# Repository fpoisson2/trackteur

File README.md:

# Trackteur

Système de traceur GPS DIY pour le suivi de véhicules et équipements agricoles. Ce projet documente la création et le déploiement d'un système de suivi GPS complet, depuis le matériel jusqu'à l'infrastructure serveur.

## Vue d'ensemble de l'infrastructure

L'architecture est conçue pour être résiliente et évolutive, en s'appuyant sur des services cloud modernes pour le routage et l'hébergement.

```mermaid
flowchart TB
    subgraph tracker["Traceur GPS DIY"]
        ESP[ESP32 + GPS + 4G LTE]
    end

    subgraph cloudflare["Cloudflare"]
        WORKER[Cloudflare Worker<br/>endpoint.trackteur.cc]
    end

    subgraph servers["Serveurs Traccar (Réplication)"]
        SRV1[Serveur 1<br/>serveur1e.trackteur.cc]
        SRV2[Serveur 2<br/>serveur2.trackteur.cc]
        SRV3[Serveur 3<br/>serveur3.trackteur.cc]
    end

    tracker -->|envoie les données| cloudflare
    cloudflare -->|route le trafic vers| SRV1
    cloudflare -->|route le trafic vers| SRV2
    cloudflare -->|route le trafic vers| SRV3
```

## Composants

| Composant | Description |
|-----------|-------------|
| **Traceur GPS DIY** | Appareil basé sur LilyGo T-A7670G (ESP32) équipé d'un module GPS et cellulaire 4G/LTE pour collecter et transmettre les coordonnées en temps réel. |
| **Cloudflare Worker** | Point d'entrée unique qui réplique les données vers plusieurs serveurs Traccar, assurant une redondance des données. |
| **Serveurs Traccar** | Instances indépendantes du serveur Traccar en Docker. Port 5055 pour OsmAnd, port 8082 pour l'interface web. |
| **Carte SIM Hologram** | Connectivité IoT mondiale avec roaming automatique et tarification optimisée. |

## Caractéristiques du firmware

- **Intervalle d'envoi**: 2 minutes (configurable)
- **Timeout GPS**: 1 minute sans fix → sleep automatique
- **Protocole**: OsmAnd (HTTPS)
- **Backup SD**: Sauvegarde CSV si échec réseau
- **Multi-constellation**: GPS, GLONASS, BeiDou, Galileo
- **Mode veille**: Modem sleep entre transmissions (2-3 mA)

## Navigation

| Guide | Description |
|-------|-------------|
| [BOM (Liste des composants)](docs/BOM.md) | Liste du matériel nécessaire |
| [Fabrication du traceur GPS](docs/fabrication_traceur_gps.md) | Instructions pour assembler le matériel |
| [Programmation du LilyGo A7670G](docs/programmation_liligo_a7670g.md) | Guide pour flasher le firmware |
| [Déploiement des serveurs Traccar](docs/installation_docker.md) | Mise en place des serveurs avec Docker |
| [Configuration de Cloudflare](docs/configuration_cloudflare.md) | Mise en place du tunnel et du Worker |
| [Création de carte SIM Hologram](docs/creation_carte_sim_hologram.md) | Activation de la SIM, APN et gestion du solde |
| [Ajout d'un appareil dans Traccar](docs/ajout_appareil_traccar.md) | Déclarer le traceur sur le serveur Traccar |
| [Installation dans un véhicule](docs/installation_vehicule.md) | Conseils pour l'installation physique |

## Installation rapide

### 1. Configuration firmware

Éditer `code/TraccarGPS/config.h`:

```cpp
#define TRACCAR_DEVICE_ID    "TRACTEUR_001"
#define TRACCAR_SERVER_URL   "https://endpoint.trackteur.cc"
#define NETWORK_APN          "hologram"
```

### 2. Compilation et upload

```bash
arduino-cli compile --fqbn esp32:esp32:esp32 code/TraccarGPS/
arduino-cli upload --fqbn esp32:esp32:esp32 --port /dev/ttyACM0 code/TraccarGPS/
```

### 3. Déploiement serveur

```bash
docker-compose up -d
```

## Structure du projet

```
trackteur/
├── code/TraccarGPS/        # Firmware Arduino
├── docs/                   # Documentation MkDocs
├── docker-compose.yml      # Déploiement serveurs
└── mkdocs.yml              # Configuration documentation
```

## Documentation en ligne

La documentation complète est disponible sur [https://trackteur.cc](https://trackteur.cc)

## Licence

MIT License

## Remerciements

- [LilyGo](https://github.com/Xinyuan-LilyGO) - Module T-A7670G et fork TinyGSM
- [Traccar](https://www.traccar.org/) - Plateforme de tracking open-source
- [Hologram](https://www.hologram.io/) - Connectivité IoT globale

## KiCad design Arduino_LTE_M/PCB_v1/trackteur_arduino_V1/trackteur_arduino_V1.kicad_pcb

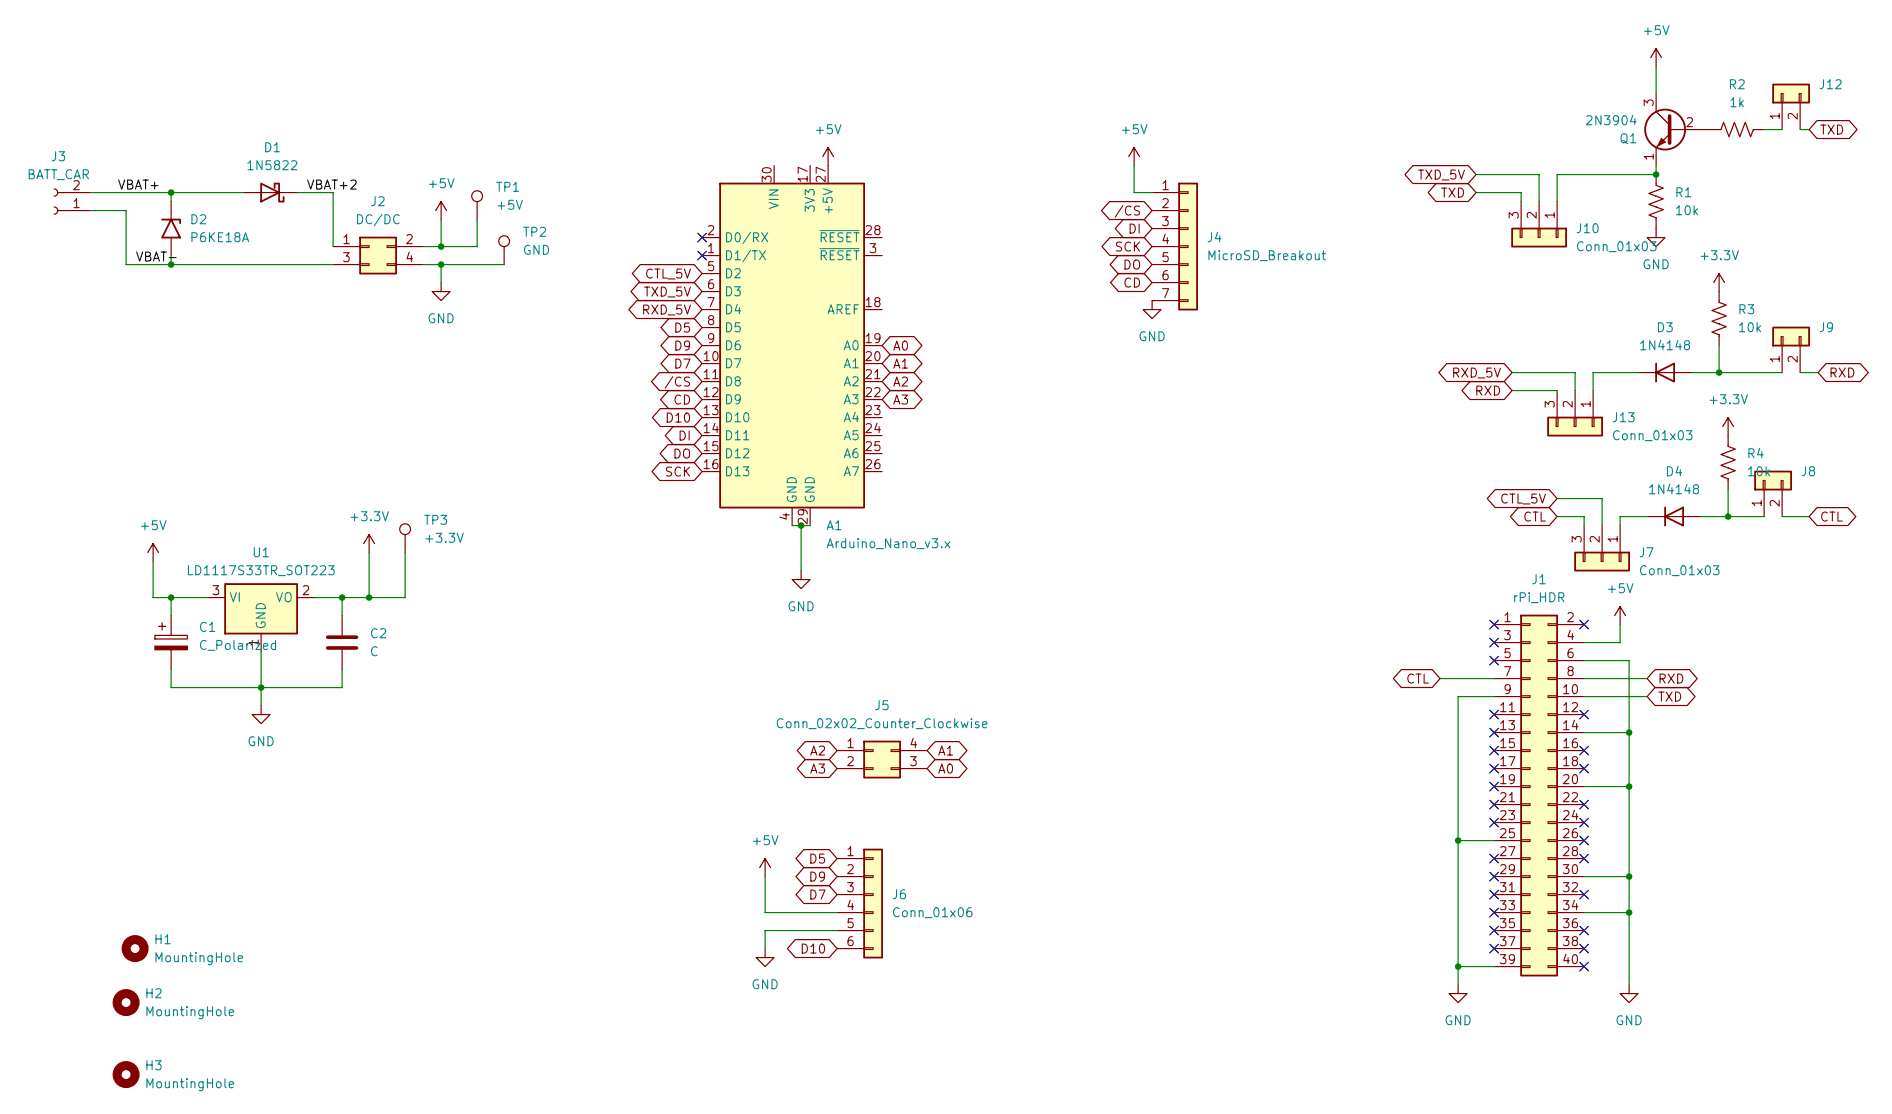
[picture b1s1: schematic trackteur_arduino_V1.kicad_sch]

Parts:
A1: Arduino_Nano_v3.x; Arduino_Nano
C1: C_Polarized; CP_Radial_D5.0mm_P2.50mm
C2: C; C_Disc_D5.0mm_W2.5mm_P5.00mm
D1: 1N5822; D_DO-201AD_P15.24mm_Horizontal
D2: P6KE18A; D_DO-15_P12.70mm_Horizontal
D3, D4: 1N4148; D_DO-35_SOD27_P7.62mm_Horizontal
H1, H2, H3: MountingHole; MountingHole_2.7mm_M2.5
J1: rPi_HDR; PinHeader_2x20_P2.54mm_Vertical
J2: DC/DC; LM2596_DC_DC_MODULE
J3: BATT_CAR; TE_282837-2
J4: MicroSD_Breakout; PinHeader_1x07_P2.54mm_Vertical
J5: Conn_02x02_Counter_Clockwise; PinHeader_2x02_P2.54mm_Vertical
J6: Conn_01x06; PinHeader_1x06_P2.54mm_Vertical
J7, J10, J13: Conn_01x03; PinHeader_1x03_P2.54mm_Vertical
J8, J9, J12: Conn_01x02; PinHeader_1x02_P2.54mm_Vertical
Q1: 2N3904; TO-92_Inline
R1, R3, R4: 10k; R_Axial_DIN0207_L6.3mm_D2.5mm_P10.16mm_Horizontal
R2: 1k; R_Axial_DIN0207_L6.3mm_D2.5mm_P10.16mm_Horizontal
TP1: +5V; PinHeader_1x01_P2.54mm_Vertical
TP2: GND; PinHeader_1x01_P2.54mm_Vertical
TP3: +3.3V; PinHeader_1x01_P2.54mm_Vertical
U1: LD1117S33TR_SOT223; TO-220-3_Vertical

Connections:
+3.3V: C2.1, R3.2, R4.2, TP3.1, U1.2 (VO)
+5V: A1.27 (+5V), C1.1, J1.4, J2.2, J4.1, J6.4, Q1.3 (C), TP1.1, U1.3 (VI)
/VBAT+: D1.2 (A), D2.1 (A1), J3.2
/VBAT+2: D1.1 (K), J2.1
/VBAT-: D2.2 (A2), J2.3, J3.1
A0: A1.19 (A0), J5.3
A1: A1.20 (A1), J5.4
A2: A1.21 (A2), J5.1
A3: A1.22 (A3), J5.2
CD: A1.12 (D9), J4.6
CTL: J1.7, J7.3, J8.2
CTL_5V: A1.5 (D2), J7.2
D5: A1.8 (D5), J6.1
D7: A1.10 (D7), J6.3
D9: A1.9 (D6), J6.2
D10: A1.13 (D10), J6.6
DI: A1.14 (D11), J4.3
DO: A1.15 (D12), J4.5
GND: A1.4 (GND), A1.29 (GND), C1.2, C2.2, J1.6, J1.9, J1.14, J1.20, J1.25, J1.30, J1.34, J1.39, J2.4, J4.7, J6.5, R1.1, TP2.1, U1.1 (GND)
unnamed: D3.2 (A), J9.1, R3.1
unnamed: D3.1 (K), J13.1
unnamed: D4.2 (A), J8.1, R4.1
unnamed: D4.1 (K), J7.1
unnamed: J10.1, Q1.1 (E), R1.2
unnamed: J12.1, R2.2
unnamed: Q1.2 (B), R2.1
RXD: J1.8, J9.2, J13.3
RXD_5V: A1.7 (D4), J13.2
SCK: A1.16 (D13), J4.4
TXD: J1.10, J10.3, J12.2
TXD_5V: A1.6 (D3), J10.2
/CS: A1.11 (D8), J4.2

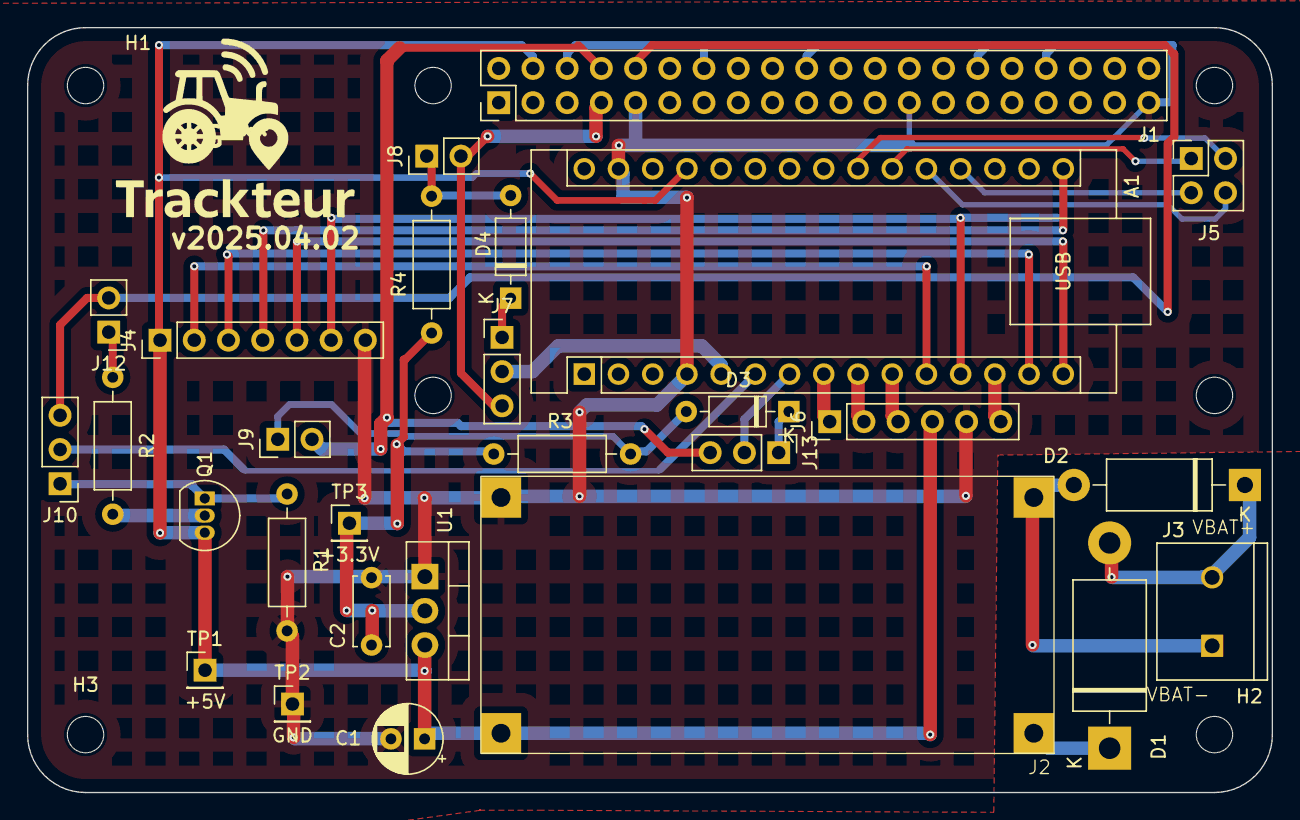
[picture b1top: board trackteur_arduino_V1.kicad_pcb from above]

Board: 2 copper layers, 92.4 x 56.8 mm, 35 parts (0 on the bottom side), 32 nets.

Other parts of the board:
H2#2, H4, H5: MountingHole_2.7mm_M2.5
H3#2: MountingHole; MountingHole_2.7mm_M2.5

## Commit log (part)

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2025-03-17 send_gps
2025-03-17 working code
2025-03-17 enhance range
2025-03-17 test SF12
2025-03-17 test lower BW
2025-03-17 test sf 12
2025-03-17 update time interval
2025-03-17 test
2025-03-17 try sf12
2025-03-17 change of CR
2025-03-17 BW of 125 kHz
2025-03-17 BW of 125 khz and CR of 4/8
2025-03-17 frequency hoping
2025-03-17 trying frequency correction
2025-03-17 test 62.5 kHz
2025-03-17 return to 125 kHz
2025-03-17 add traccar
2025-03-17 add log
2025-03-17 test ack
2025-03-17 other delays
2025-03-17 delays
2025-03-17 add delays
2025-03-17 Revert "Update tx_gps.py"
    This reverts commit 55315d07eee350d4b5e3669db003c1767ba46db4.
2025-03-17 ack correction
2025-03-17 new test ack
2025-03-17 retest ack
2025-03-17 add debug
2025-03-17 test #1000
2025-03-17 working
2025-03-17 without ack
2025-03-17 test_rx_tx
2025-03-18 correctifs
2025-03-18 CR 4/5
2025-03-18 fhss
2025-03-18 explicit header
2025-03-18 enhanced rx
2025-03-18 add test
2025-03-18 update ldro dynamically
2025-03-18 lrdo
2025-03-18 add bw 62.5
2025-03-18 typo
2025-03-18 deletee non-working files files
2025-03-18 tests
2025-03-24 update requirements.
2025-03-31 Restructure des dossiers
2025-03-31 ajout de dossiers
2025-04-02 arduino LTE-M first tests
2025-04-03 Ajout PCB
2025-04-03 update PCB
2025-04-03 Fichiers de fabrication
2025-04-03 gerberfile_zip
2025-04-03 code
2025-04-03 add logo
2025-04-04 Update send_gps_simple.ino
    working
2025-04-24 LTE send dummy gps working and new pcb
2025-04-24 update PCB gerbers
2025-04-29 new gerbers
2025-05-01 optimisation ram
2025-05-02 petitfs
2025-05-05 resend logic
2025-05-05 prob dwt
2025-05-05 refactorisation
2025-05-05 rety logic when setup failed
2025-05-05 add detection of gsm module and conneciton logic in loop for connection failover management
2025-05-06 cleanup
2025-05-06 add doc
2025-05-06 update doc
2025-05-06 deploy: 48dc43cb4ba185dea7f207f88c46ef35f06d31db
2025-05-06 deploy: 82e82b1d5b74f42937e230a362bb8b771ac76459
2025-05-06 réduction buffers
2025-05-06 deploy: a6b72da7dc49134570a6adacf841ed5f725c85df
2025-05-06 augmentation buffers
2025-05-06 deploy: 19b2387c83574fc20372fae7c1e2ab180d1a65f9
2025-05-06 deploy: 6c76a82e0b1d8d7ccd8ec090a942dc6414898cc5
2025-05-06 probleme SRAM
2025-05-06 deploy: 8c242a78f62186796aef9dfee9c515a9b18dc6b1
2025-05-06 règlage probleme SRAM
2025-05-06 deploy: f32afa17a67b549cf7708b3bc1b849ca11dcf07a
2025-05-06 working for a7670e
2025-05-06 deploy: a6aabe638dcee243f187e99baf3ba64f482bba98
2025-05-06 deploy: 9d39216c4db44be672f6bd076a164d023021b84d
2025-05-06 sim7000G works again...
2025-05-06 deploy: b92f21f576bb79fdafb7169c17475c6ace26adf8
2025-05-06 deploy: 775c01fc7665da7f07c0b87b0d0e5b7b006c7886
2025-05-07 deploy: fce286f5cd98f60101d17800d1d4715bccd9b11b
2025-05-07 detect sim7070g
2025-05-07 deploy: f2aee491fe7441d1ca2f4b80cc91c78549c2d6d6
2025-05-07 compatible sim7070g
2025-05-07 deploy: 458f63c8523a2a820a4cf3602f98e6f85eadd8d2
2025-05-08 Fonctionne pour SIM7000G, SIM707G et A7670E
2025-05-08 deploy: 58d6ec963fb5fa7d27b1ccc45f80227a7185363e
2025-05-08 deploy: 24e9de4b7c009a6c6b9684f69f7d2f01dfb7833f
2025-05-08 deploy: 71e0f9229e601d204b19588f685eff82597513e4
2025-05-08 Révision séquence power-up
2025-05-08 deploy: 95b80658a715cf29b6d66e28ffff3667892e4927
2025-05-11 nettoyage logs
2025-05-11 deploy: 4e8c76e0a6b82b97f7f657629eb615cf369a17e2
2025-05-11 déplacement des paramètes importants
2025-05-11 deploy: 32ef4e96bcb4f6995eabd9d553a031546005a058
2025-05-11 deploy: ff06c71777f1af94cab2615bf469267d76f5c563
2025-05-11 oublie ca
2025-05-11 deploy: 9c2bde636ac70eb876a44c4276cc18f96687cb3c
2025-05-13 seems to have a bug with sim7000g
2025-05-13 deploy: b16b6263726aeca079eba6c8d20ccd5b2de54f73
2025-05-13 réglagle du problème avec le sim7000g
2025-05-13 deploy: 000c5a422176b097d8f596330d344d9d1893a563
2025-05-13 ajout config file
2025-05-13 deploy: 78315a7aef877b8bfb322ef9e4ec61e327f2b599
2025-05-13 deploy: 8528378a781f131e142426922cb08084630c1eb3
2025-05-13 Ajout commentaires
2025-05-13 deploy: 63eaab4ff3e017738a117aa3b5d07a7bf78b1db3
2025-05-14 seems to work
2025-05-14 deploy: c74f8c1da978dcb683ce50def1cfb3597bad1a1a
2025-05-14 deploy: 80ee95d5e9a12416994371d590b8fe3ae99e472c
2025-05-14 deploy: ffa4d1ed24ba5f33eead4f94ba951d4b6383fdea
2025-05-14 deploy: 0f5d5d0d4359d2308b5564e5a5be49366b52ba87
2025-05-15 reboot lorsqu'offline
2025-05-15 deploy: 8ce07f09e28b0456720127a4bd5ec0fc74f45452
2025-05-15 deploy: 96dec47fcfe282cabe996dbed80396726cc861f8
2025-05-15 ajout librairie PF
2025-05-15 deploy: 24fb8e1db676269a510af1175fc7f0c6606aa48d
2025-05-15 deploy: c32777aca5a7b78af4694a6af4c2c6f7662ce27f
2025-06-06 deploy: 4104e307d5dff94beaf4ced4d86d91eaa57969f0
2025-06-06 deploy: 14fcab4091ab9664b658a4e90f81171c67754aec
2025-06-07 ca semble bon, je cherche les bogues...
2025-06-07 deploy: a86396b7db33379087a070fe3eef496cec6b94e3
2025-06-07 deploy: 02e1efbce82f853de3e1c340b070311212f8c161
2025-07-07 new version test
2025-07-07 deploy: 6ae5583e63fd144e2dd0feb57ab8947b70fe2ad4
2025-07-07 deploy: 43434c4bf6c53b2308a1469ecdd3b377992c1074
2025-07-08 deploy: ce3f6effe245ada9073e3ffb6abc3eb18ae2969a
2025-07-08 deploy: 1d8ad6dd0e067a9474add2278fdc76949c705af2
2025-07-10 deploy: 7583a4301d53450c88fc30c99585f26047509336
2025-07-10 deploy: 910a453a57bdcf9ce51bb40d00e8a7cec4c1094b
2025-07-10 deploy: 0cd754be56c94d3ee3666dadb6db135841686536
2025-08-12 deploy: 37faf9c7b0dec3ff8e897ed166974823ed17793f
2025-12-04 Add Docker Compose setup for vehicle tracking system
    Added Docker Compose configuration for Traccar vehicle tracking system, including services for database, Traccar, cloudflared, and autoheal.
2025-12-08 Add Ubuntu Docker installation steps
2025-12-08 feat: Add GPS commands and update Traccar URL
2025-12-08 docs: Add gemini.md with project information
2025-12-08 docs: Restructure documentation
2025-12-08 deploy: 8cd8615bd6e2f28b4c3a9b7cef50e2cb457c6ce9
2025-12-08 docs: Update Cloudflare configuration with Tunnels
2025-12-08 deploy: 258818a98fc0973b27bb589da458f2897014b640
2025-12-08 feat: Add docker-compose for traccar deployment
    This commit introduces a `docker-compose.yml` file to easily deploy Traccar with a MySQL database, Cloudflare tunnel for secure access, and Autoheal for container monitoring.
    The documentation has been updated to reflect these changes, including:
    - A new guide on how to use the `docker-compose.yml` file.
    - Updated Cloudflare documentation to explain the tunnel setup.
    - Removal of the old installation guide.
2025-12-08 deploy: 483a217c7380a9ffa32de3fe5e237d8c14166763
2025-12-08 docs: Refactor documentation to remove duplication
    The documentation in `index.md` and `configuration_cloudflare.md` was largely duplicated.
    This commit refactors the documentation to:
    - Keep `index.md` as the main entry point with installation and usage instructions.
    - Move all Cloudflare-specific configuration to `configuration_cloudflare.md`.
2025-12-08 deploy: ea9ebbb4074db2e67f82361992bbcb906043138c
2025-12-08 docs: Re-organize documentation for clarity
    This commit restructures the documentation to be more user-friendly and provide a clearer overview of the project.
    - The `index.md` file is now a high-level overview of the project infrastructure, including a Mermaid graph.
    - The detailed Docker installation instructions have been moved to a new `installation_docker.md` file.
    - The `mkdocs.yml` navigation has been updated to reflect these changes and provide a more logical flow.
2025-12-08 deploy: d91c79e803f8b41d91ae83fb2f6ddbed941aa664
2025-12-08 Create CNAME
2025-12-08 docs: Add support for Mermaid diagrams
    This commit adds support for Mermaid diagrams to the documentation site.
    It updates `mkdocs.yml` with the necessary plugin and markdown extensions to render Mermaid graphs.
2025-12-08 docs: Try different mermaid plugin
    The mermaid diagram is not rendering. This commit attempts to fix the issue by switching from `mkdocs-mermaid2-plugin` to `mkdocs-mermaid-plugin`, which might have better compatibility with the build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
2025-12-08 fix(docs): Add missing dependencies for mermaid rendering
    The mermaid diagram was not rendering on GitHub Pages because the required plugins were not installed during the build process.
    This commit fixes the issue by:
    - Updating the GitHub Actions workflow to install `mkdocs-mermaid2-plugin` and `pymdown-extensions`.
    - Reverting `mkdocs.yml` to use the `mermaid2` plugin.
2025-12-08 deploy: a331f01367bdd8a8baf00e3a3020bf3d75020d71
2025-12-08 ci(docs): Add custom domain to deployment workflow
    This commit updates the GitHub Actions workflow to include the custom domain `docs.trackteur.cc` in the deployment process.
2025-12-08 deploy: 85730bfc1ed6ea883e4040982de9832198e1c6cc
2025-12-16 deploy: bdbac802f4360f7e1516a2516554d77b94f18aee
2025-12-17 Update docs
2025-12-17 deploy: bd56d1868b229d37af1d161d5add746451e4e49c
2025-12-17 deploy: 28367d27aa1642fdf3f6301a0e3443710d4f29dc
2025-12-17 deploy: 24050178dced6acee58ae263715b29f87ea62b87
2026-03-26 deploy: 37b0db11416484643d62752fa4b6f80c7706411c
2026-03-26 Remove image from README
    Removed an image from the README file.
2026-03-26 deploy: df4e786cf40ca1e4cdf4f8c28a08e19551ce7176
2026-06-16 Revise assembly steps and installation details
    Updated assembly steps for the GPS tracker, including detailed instructions for component installation and wiring.
2026-06-16 deploy: da55b49d6c993c7e4e65c20de3e448a7d7ab6e4f
2026-06-16 deploy: 281e0d7bd677250e05590ad906e228378dad999c
